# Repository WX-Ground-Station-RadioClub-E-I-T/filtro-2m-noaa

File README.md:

# Filtro-2m-NOAA

Filtro paso banda para banda de radioaficionados de 2m y satélites NOAA/Meteor, con alto rechazo en zona de frecuencias de radiodifusión FM.

## Especificaciones

- Tipo: Tchebyshev

- Impedancia entrada/salida: 50 Ohm

- Frecuencia de corte inferior (3dB): 125MHz

- Frecuencia de corte superior (3dB): 150MHz

- Pérdidas de inserción: 1dB máx.

- S11 en banda de paso: -15dB máx.

- Rechazo banda radiodifusión FM: 45dB (min)

- Rechazo banda radiodifusión TV: 50dB (min)

## Materiales

| Componente | Valor | Métrica |
|:----------:|:-----:|:-------:|
|     C1     |  10pF |   0805  |
|     C2     | 2,7pF |   0805  |
|     C3     | 2,2pF |   0603  |
|     C4     |  10pF |   0805  |
|     C5     | 1,5pF |   0603  |
|     C6     |  10pF |   0805  |
|     C7     | 2,2pF |   0603  |
|     C8     | 2,7pF |   0805  |
|     C9     |  10pF |   0805  |
|     L1     | 100nH |   0603  |
|     L2     | 100nH |   0603  |
|     L3     | 100nH |   0603  |
|     L4     | 100nH |   0603  |
|     L5     | 100nH |   0603  |
|  Conector  |  SMA  |    -    |

## Resultados

Parmámetros S:

Esquemático: 

Modelo 3D:

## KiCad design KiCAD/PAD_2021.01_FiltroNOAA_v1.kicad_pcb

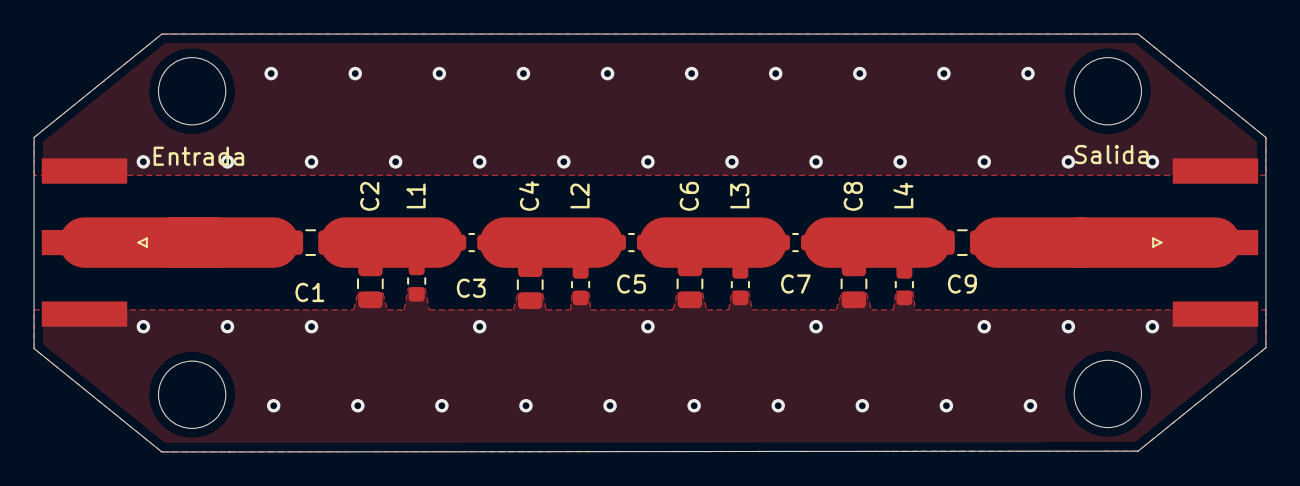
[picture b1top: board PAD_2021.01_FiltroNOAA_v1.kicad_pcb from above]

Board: 2 copper layers, 73.2 x 24.9 mm, 15 parts (0 on the bottom side), 7 nets.

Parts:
C1, C4, C6, C9: 10pF; C_0805_2012Metric
C2, C8: 2,7pF; C_0805_2012Metric
C3, C7: 2,2pF; C_0603_1608Metric
C5: 1,5pF; C_0603_1608Metric
Entrada: Conn_Coaxial; SMA_Amphenol_132289_EdgeMount
L1, L2, L3, L4: 100nH; L_0603_1608Metric
Salida: Conn_Coaxial; SMA_Amphenol_132289_EdgeMount

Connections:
Earth: C2.2, C4.2, C6.2, C8.2, Entrada.2, L1.2, L2.2, L3.2, L4.2, Salida.2
unnamed: C1.1, C2.1, C3.2, L1.1
unnamed: C1.2, Entrada.1
unnamed: C3.1, C4.1, C5.2, L2.1
unnamed: C5.1, C6.1, C7.2, L3.1
unnamed: C7.1, C8.1, C9.2, L4.1
unnamed: C9.1, Salida.1

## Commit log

2021-01-19 Subir archivos a 'KiCAD'
2021-01-19 Actualizar 'README.md'
2021-01-19 Subir archivos a 'ADS'
2021-01-19 Subir archivos a 'ADS/PAD_2021.01_FiltroRadio_lib'
2021-01-19 Subir archivos a 'ADS/PAD_2021.01_FiltroRadio_lib/%Filtro_tb/schematic'
2021-01-19 Subir archivos a 'ADS/PAD_2021.01_FiltroRadio_lib/filtro_teorico/schematic'
2021-01-19 Subir archivos a 'ADS/PAD_2021.01_FiltroRadio_lib/filtro_teorico/symbol'
2021-01-19 Subir archivos a 'ADS/data'
2021-01-19 Subir archivos a 'resultados'
2021-01-19 Subir archivos a 'Gerbers'
